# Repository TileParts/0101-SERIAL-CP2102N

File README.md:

0101-SERIAL-CP2102N
==========

基于 CP2102N 的 USB-UART 转接器，并且附带 ESP32 兼容的自动烧录电路。

## 配置

SERIAL-CP2102N 背面预留了可配置的电路，可将 DTR/RTS 更改为用于 ESP32 自动烧录的 EN/IO0 功能。具体如下：

| 功能 | R8/R9 | Q1 |
|-----|-----|-----|
| 用作 DTR/RTS | 焊接 0Ω 0603 电阻 | 留空 |
| 用作 ESP32 烧录 | 留空 | 焊接 PUMH4,115 |

## 协议

[CERN-OHL-P-2.0](LICENSE)

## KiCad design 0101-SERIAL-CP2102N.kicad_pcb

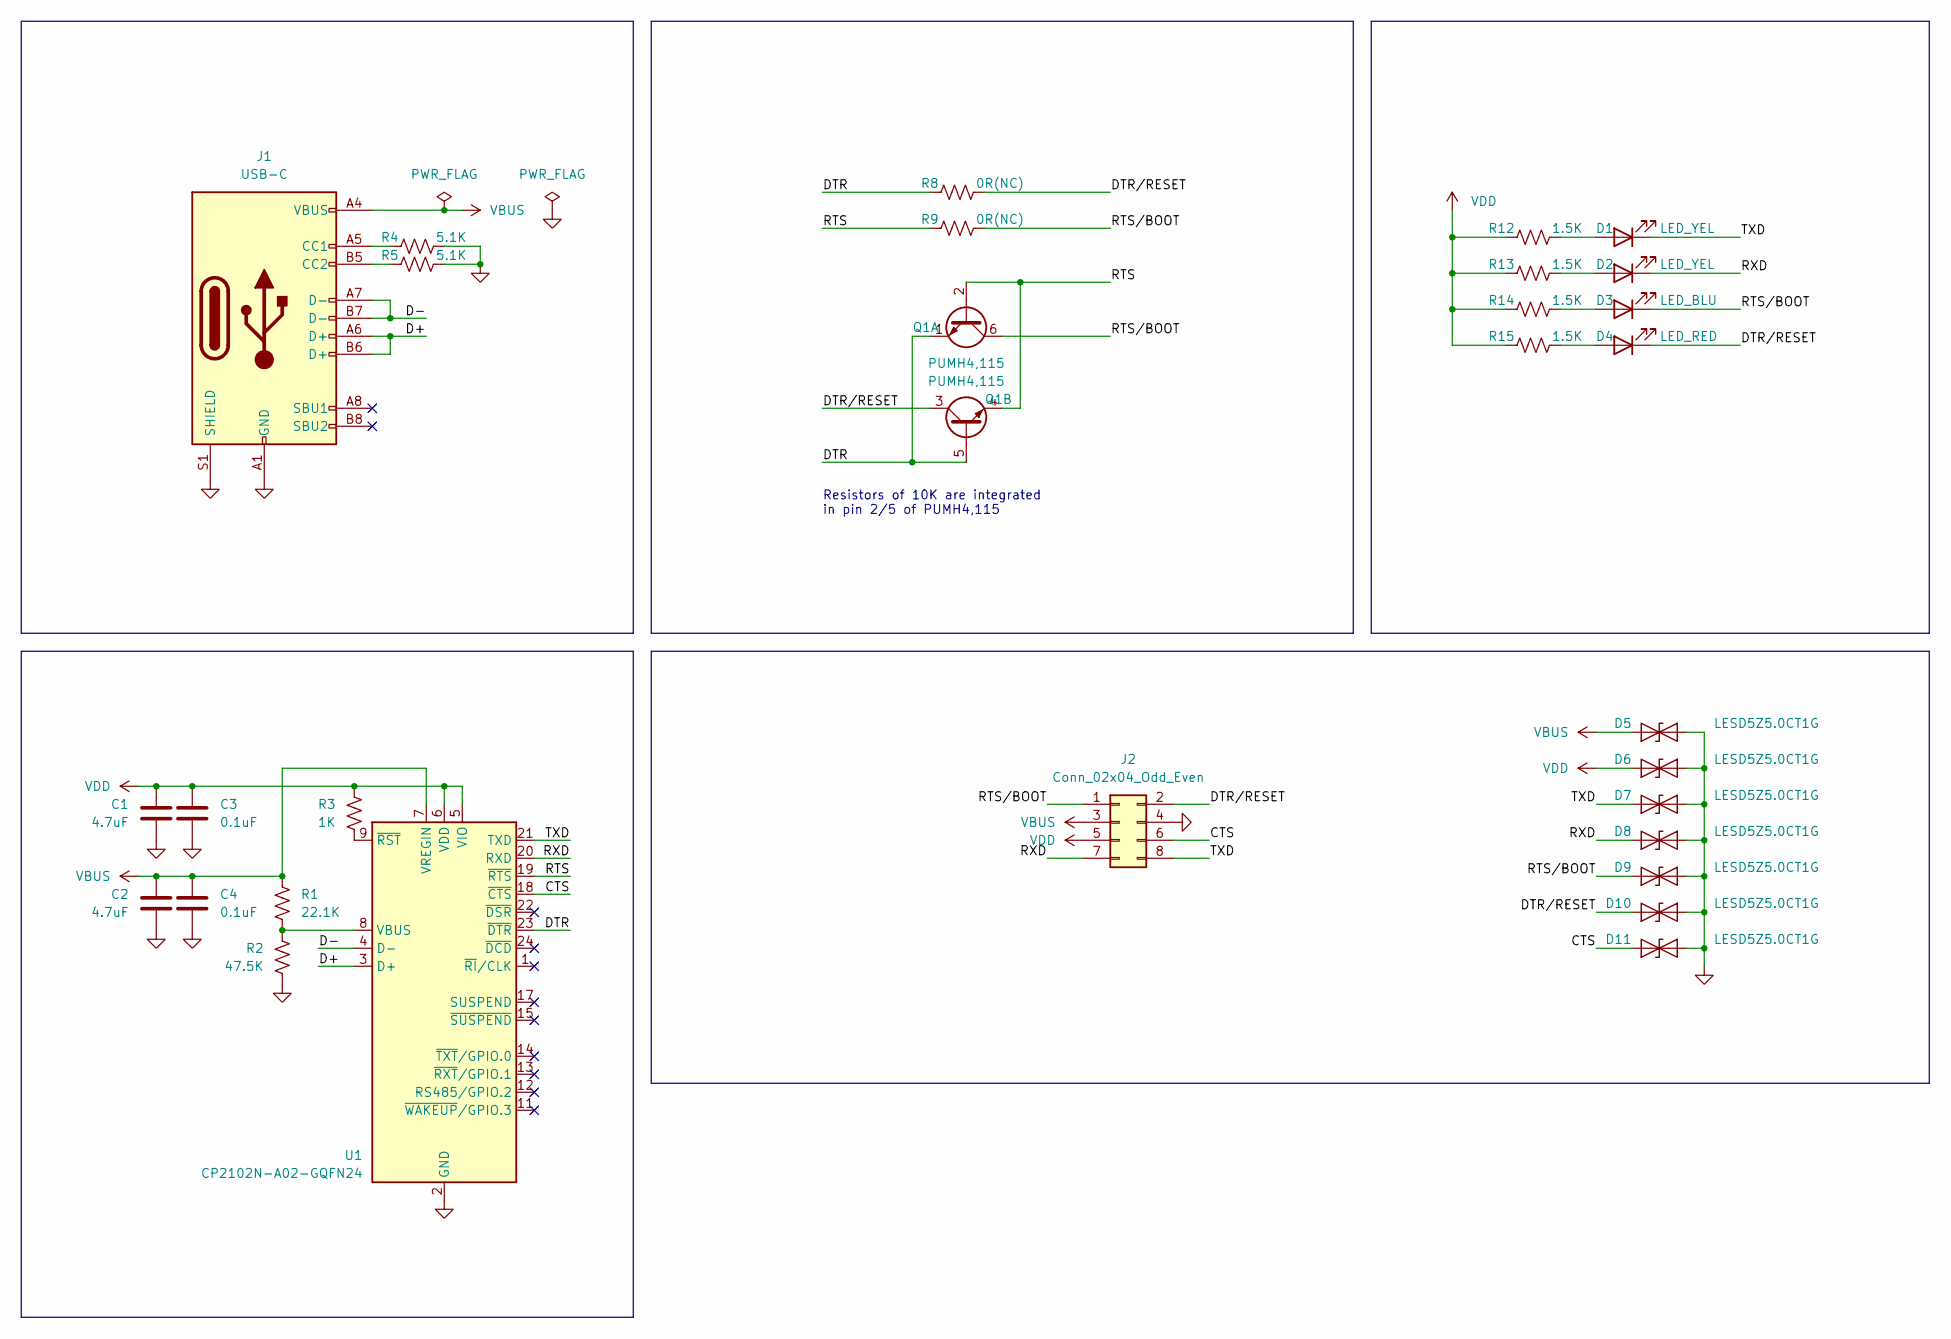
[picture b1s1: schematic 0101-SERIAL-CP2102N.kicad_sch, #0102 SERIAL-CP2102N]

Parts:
C1, C2: 4.7uF; C_0402_1005Metric; PartNumber C23733
C3, C4: 0.1uF; C_0402_1005Metric; PartNumber C1525
D1, D2: LED_YEL; LED_0603_1608Metric; PartNumber C72038
D3: LED_BLU; LED_0603_1608Metric; PartNumber C72041
D4: LED_RED; LED_0603_1608Metric; PartNumber C2286
D5, D6, D7, D8, D9, D10, D11: LESD5Z5.0CT1G; D_SOD-523; PartNumber C136167
J1: USB-C; HRO_TYPE-C-31-M-12; PartNumber C165948
J2: Conn_02x04_Odd_Even; PinHeader_2x04_P2.54mm_Vertical
Q1: PUMH4,115; SOT-363_SC-70-6; PartNumber C455002
R1: 22.1K; R_0402_1005Metric; PartNumber C43473
R2: 47.5K; R_0402_1005Metric; PartNumber C25896
R3: 1K; R_0402_1005Metric; PartNumber C11702
R4, R5: 5.1K; R_0402_1005Metric; PartNumber C25905
R8, R9: 0R(NC); R_0603_1608Metric; PartNumber C21189
R12, R13, R14, R15: 1.5K; R_0402_1005Metric; PartNumber C25867
U1: CP2102N-A02-GQFN24; QFN-24-1EP_4x4mm_P0.5mm_EP2.6x2.6mm; PartNumber C969151

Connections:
/CTS: D11.2 (A2), J2.6, U1.18 (~CTS)
/D+: J1.A6 (D+), J1.B6 (D+), U1.3 (D+)
/D-: J1.A7 (D-), J1.B7 (D-), U1.4 (D-)
/DTR: Q1.1 (E1), Q1.5 (B2), R8.1, U1.23 (~DTR)
/DTR/RESET: D4.1 (K), D10.2 (A2), J2.2, Q1.3 (C2), R8.2
/RTS: Q1.2 (B1), Q1.4 (E2), R9.1, U1.19 (~RTS)
/RTS/BOOT: D3.1 (K), D9.2 (A2), J2.1, Q1.6 (C1), R9.2
/RXD: D2.1 (K), D8.2 (A2), J2.7, U1.20 (RXD)
/TXD: D1.1 (K), D7.2 (A2), J2.8, U1.21 (TXD)
GND: C1.2, C2.2, C3.2, C4.2, D5.1 (A1), D6.1 (A1), D7.1 (A1), D8.1 (A1), D9.1 (A1), D10.1 (A1), D11.1 (A1), J1.A1 (GND), J1.A12 (GND), J1.B1 (GND), J1.B12 (GND), J1.S1 (SHIELD), J2.4, R2.2, R4.2, R5.2, U1.2 (GND), U1.25 (GND)
unnamed: D1.2 (A), R12.2
unnamed: D2.2 (A), R13.2
unnamed: D3.2 (A), R14.2
unnamed: D4.2 (A), R15.2
unnamed: J1.A5 (CC1), R4.1
unnamed: J1.B5 (CC2), R5.1
unnamed: R1.2, R2.1, U1.8 (VBUS)
unnamed: R3.2, U1.9 (~RST)
VBUS: C2.1, C4.1, D5.2 (A2), J1.A4 (VBUS), J1.A9 (VBUS), J1.B4 (VBUS), J1.B9 (VBUS), J2.3, R1.1, U1.7 (VREGIN)
VDD: C1.1, C3.1, D6.2 (A2), J2.5, R3.1, R12.1, R13.1, R14.1, R15.1, U1.5 (VIO), U1.6 (VDD)

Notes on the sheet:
Resistors of 10K are integrated in pin 2/5 of PUMH4,115

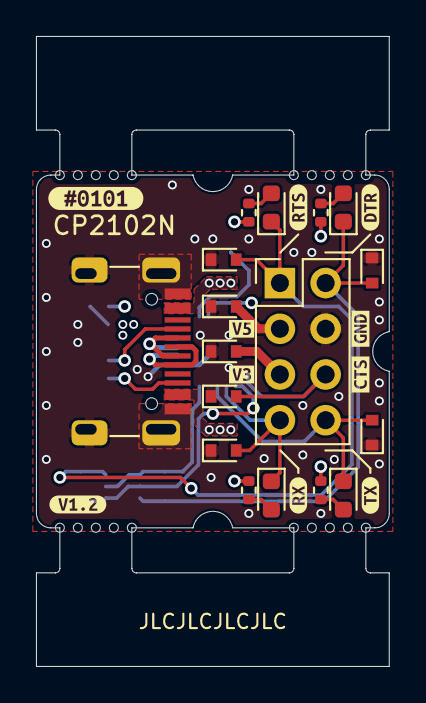
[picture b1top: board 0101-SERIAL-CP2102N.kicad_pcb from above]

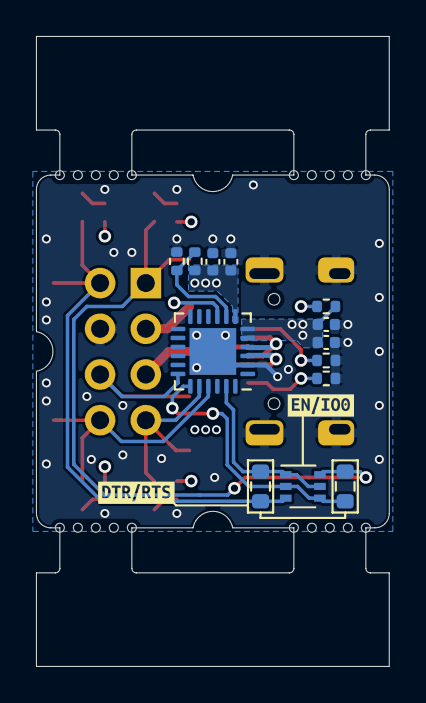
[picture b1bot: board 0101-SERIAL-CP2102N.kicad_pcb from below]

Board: 4 copper layers, 19.6 x 35.0 mm, 42 parts (15 on the bottom side), 20 nets.

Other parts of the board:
kibuzzard-633A4DBF: G***; kibuzzard-633A4DBF
kibuzzard-633A4E09: G***; kibuzzard-633A4E09
kibuzzard-6344EE6E: G***; kibuzzard-6344EE6E
kibuzzard-6344EE61: G***; kibuzzard-6344EE61
kibuzzard-6344EEF9: G***; kibuzzard-6344EEF9
kibuzzard-6344EF12: G***; kibuzzard-6344EF12
kibuzzard-63351A8A: G***; kibuzzard-63351A8A
kibuzzard-63353A29: G***; kibuzzard-63353A29
kibuzzard-63353A37: G***; kibuzzard-63353A37
kibuzzard-6339534D: G***; kibuzzard-6339534D
kibuzzard-6346685F: G***; kibuzzard-6346685F
kibuzzard-63395349: G***; kibuzzard-63395349

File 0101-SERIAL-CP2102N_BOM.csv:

Manufacturer,Comment,Designator,Footprint,Quantity,PartNumber,Supplier
SAMSUNG,0.1uF,C3 C4,C_0402_1005Metric,2,C1525,JLC
SAMSUNG,4.7uF,C1 C2,C_0402_1005Metric,2,C23733,JLC
EVERLIGHT,LED_BLU,D3,LED_0603_1608Metric,1,C72041,JLC
EVERLIGHT,LED_YEL,D1 D2,LED_0603_1608Metric,2,C72038,JLC
KENTO,LED_RED,D4,LED_0603_1608Metric,1,C2286,JLC
UniOhm,1K,R3,R_0402_1005Metric,1,C11702,JLC
UniOhm,1.5K,R12 R13 R14 R15,R_0402_1005Metric,4,C25867,JLC
UniOhm,5.1K,R4 R5,R_0402_1005Metric,2,C25905,JLC
UniOhm,0R(NC),R8 R9,R_0603_1608Metric,2,C21189,JLC
LRC,LESD5Z5.0CT1G,D5 D6 D7 D8 D9 D10 D11,D_SOD-523,7,C136167,JLC-EXT
HRO,USB-C,J1,HRO_TYPE-C-31-M-12,1,C165948,JLC-EXT
SILICON LABS,CP2102N-A02-GQFN24,U1,QFN-24-1EP_4x4mm_P0.5mm_EP2.6x2.6mm,1,C969151,JLC-EXT
UniOhm,22.1K,R1,R_0402_1005Metric,1,C43473,JLC-EXT
UniOhm,47.5K,R2,R_0402_1005Metric,1,C25896,JLC-EXT
Nexperia,"PUMH4,115",Q1 Q1,SOT-363_SC-70-6,2,C455002,JLC-EXT

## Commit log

2022-09-29 Create repository
2022-09-29 Create CP2102N
2022-10-02 Done PCB
2022-10-02 Finish BOM
2022-10-03 Finish silks
2022-10-03 Add README
2022-10-03 Output docs
2022-10-03 Adjust position of LEDs
2022-10-03 Add craft edge
2022-10-03 Update docs
2022-10-04 Update render image
2022-10-06 Update package of USB-C
2022-10-07 Tune power tracks
2022-10-11 Move CC 5.1K pull-down resistors to B.Cu
    * so that they can be soldered together with CP2102N
2022-10-11 Make silks better
2022-10-12 Fix outline
2022-10-19 Add config
